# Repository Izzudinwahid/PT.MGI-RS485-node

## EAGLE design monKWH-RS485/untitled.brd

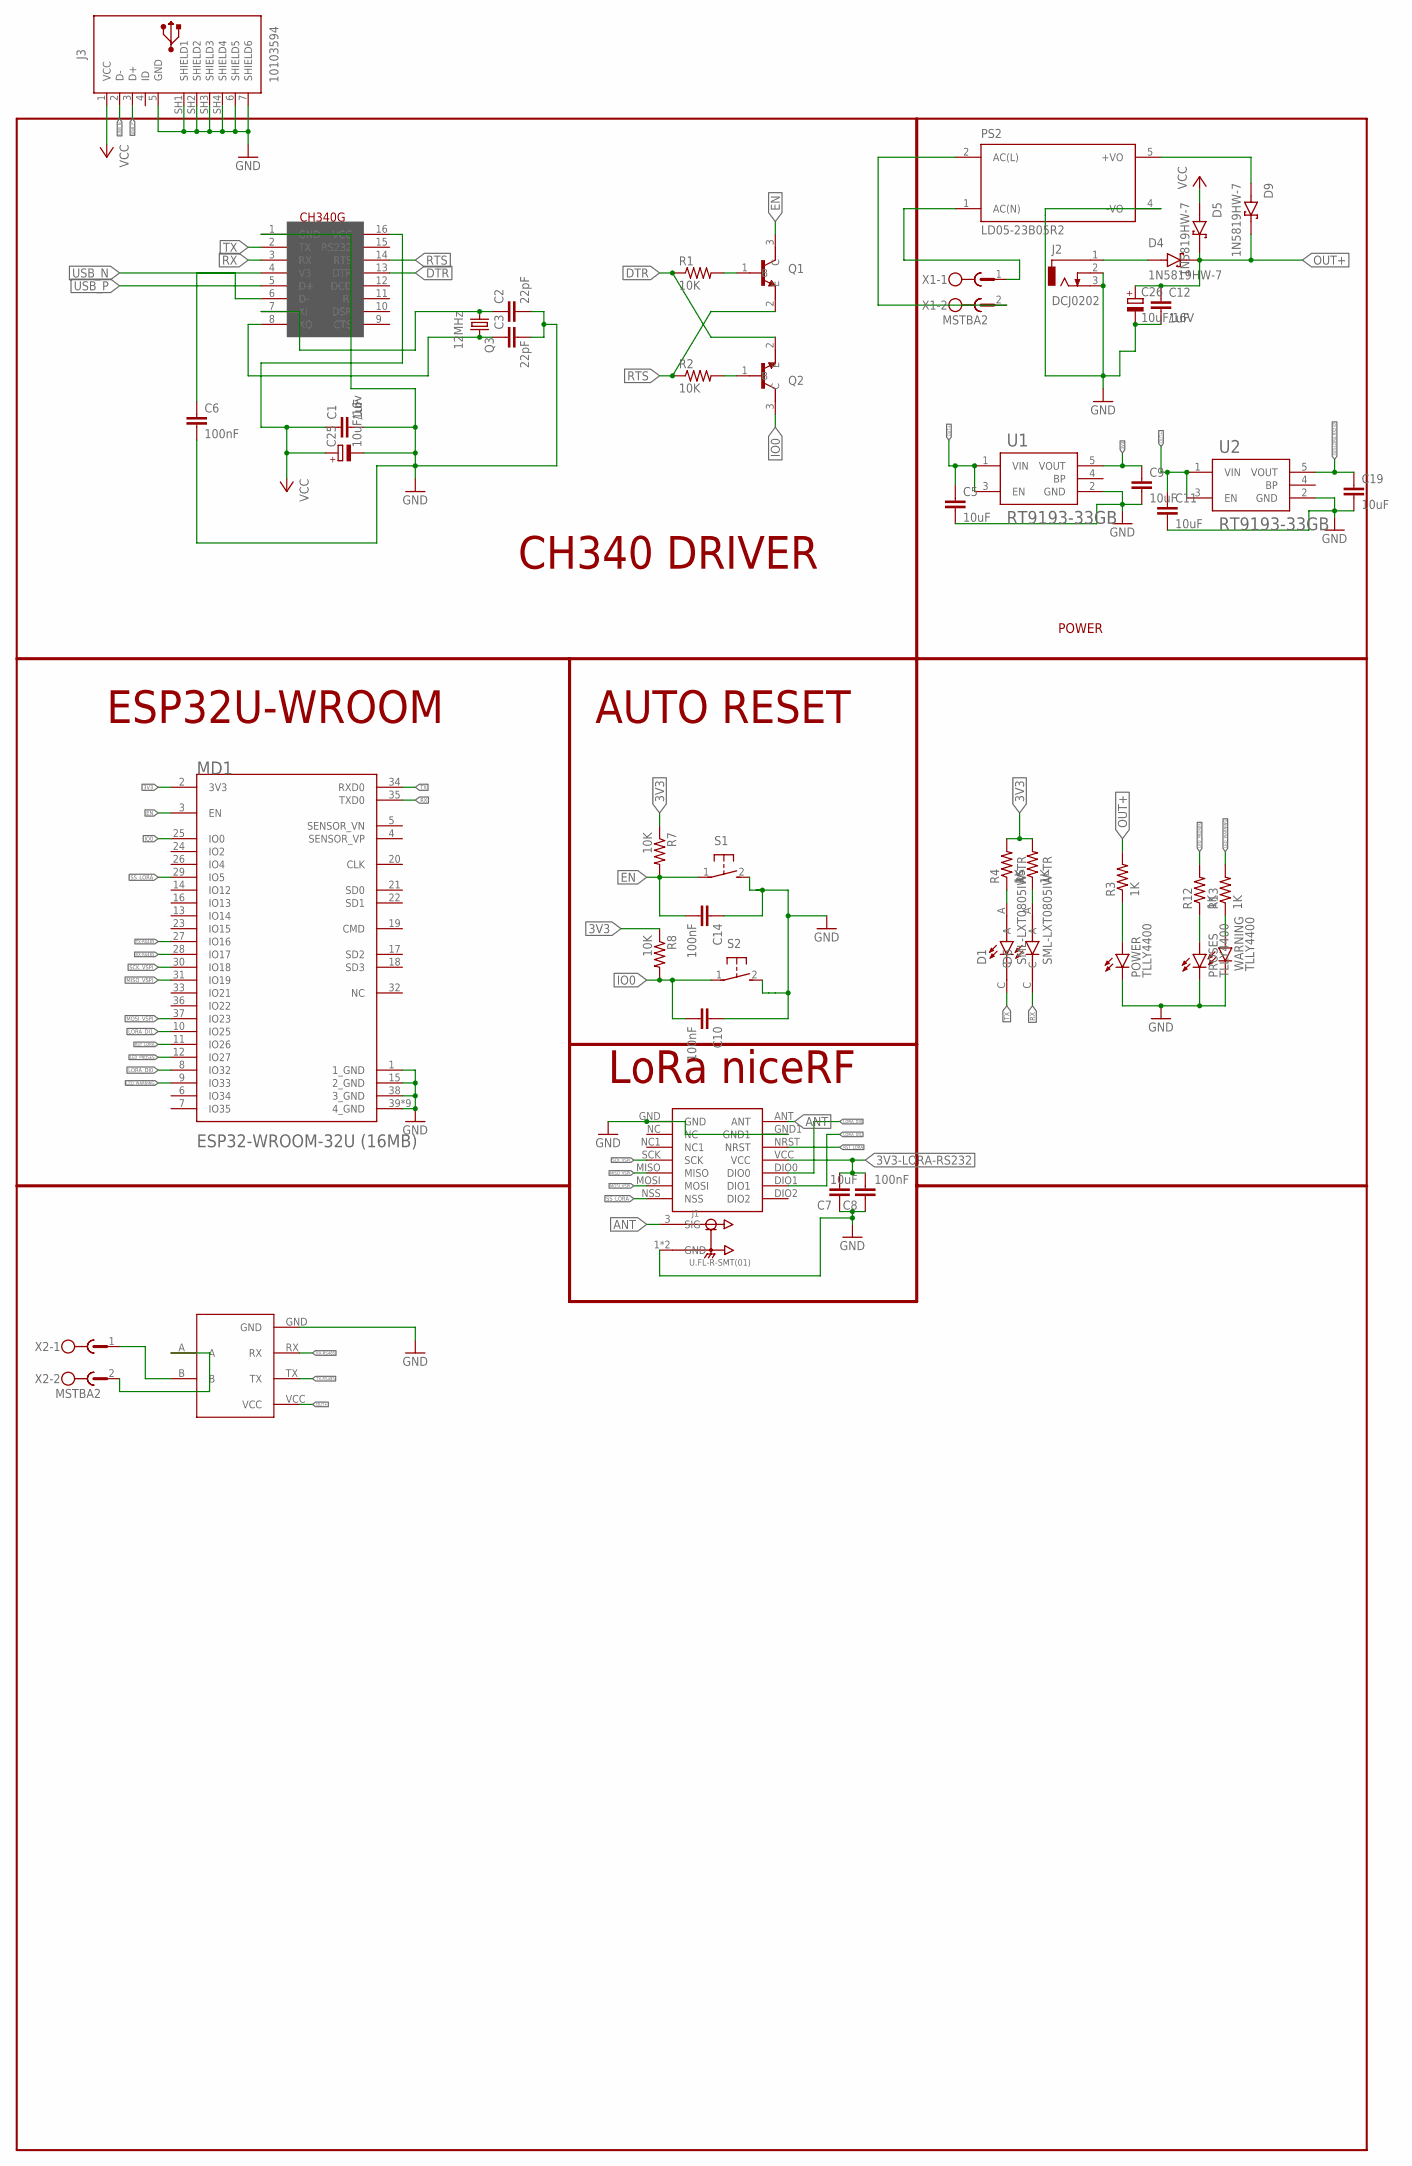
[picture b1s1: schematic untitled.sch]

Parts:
C1, C12: 1uF; C0805K
C2, C3: 22pF; C0805K
C5, C7, C9, C11, C19: 10uF; C0805K
C6, C8, C10, C14: 100nF; C0805K
C25: 10uF/16v; 153CLV-0505
C26: 10uF/16V; 153CLV-0505
D1, D6: SML-LXT0805IW-TR; LEDC2012X120N
D4, D5, D9: 1N5819HW-7; SOD3715X145N
J1: U.FL-R-SMT(01); HRS_U.FL-R-SMT(01)
J2: DCJ0202
J3: 10103594
LORA-NICERF-V1: LORA-NICERF-V2
MD1: ESPRESSIF_SYSTEMS_ESP32-WROOM-32U_16MBESPRESSIF_S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; ESPRESSIF_SYSTEMS_ESP32-WROOM-32U_16MB_0
POWER: TLLY4400; LED3MM
PROSES: TLLY4400; LED3MM
PS2: LD05-23B05R2; CONV_LD05-23B05R2
Q1, Q2: MMBT3904; SOT95P240X120-3N
Q3: 12MHz; SM49
R1, R2, R7, R8: 10K; M0805
R3, R4, R5, R12, R13: 1K; M0805
S1, S2: 31-XX; B3F-31XX
TTL-RS1: TTL-RS485
U1, U2: RT9193-33GB; SOT94P279X129-5N
U$2: CH340G; SOIC16
WARNING: TLLY4400; LED3MM
X1, X2: MSTBA2

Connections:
3V3: C9.1, MD1.2 (3V3), R4.2, R5.2, R7.1, R8.1, U1.5 (VOUT)
3V3-LORA-RS232: C7.2, C8.2, C19.1, LORA-NICERF-V1.VCC, U2.5 (VOUT)
ANT: J1.3 (SIG), LORA-NICERF-V1.ANT
DTR: Q2.2 (E), R1.1, U$2.13 (DTR)
EN: C14.2, MD1.3 (EN), Q1.3 (C), R7.2, S1.1
GND: C1.2, C2.2, C3.2, C5.2, C6.2, C7.1, C8.1, C9.2, C10.1, C11.2, C12.2, C14.1, C19.2, C25.-, C26.-, J1.1 (GND), J1.2 (GND), J2.2, J2.3, J3.5 (GND), J3.6 (SHIELD5), J3.7 (SHIELD6), J3.SH1 (SHIELD1), J3.SH2 (SHIELD2), J3.SH3 (SHIELD3), J3.SH4 (SHIELD4), LORA-NICERF-V1.GND, LORA-NICERF-V1.GND1, MD1.1 (1_GND), MD1.15 (2_GND), MD1.38 (3_GND), MD1.39 (4_GND), MD1.39-2 (4_GND), MD1.39-3 (4_GND), MD1.39-4 (4_GND), MD1.39-5 (4_GND), MD1.39-6 (4_GND), MD1.39-7 (4_GND), MD1.39-8 (4_GND), MD1.39-9 (4_GND), POWER.K (C), PROSES.K (C), PS2.4 (-VO), S1.2 (S), S2.2 (S), TTL-RS1.GND, U1.2 (GND), U2.2 (GND), U$2.1 (GND), WARNING.K (C)
IO0: C10.2, MD1.25 (IO0), Q2.3 (C), R8.2, S2.1
LED_PROSES: MD1.12 (IO27), R12.2
LED_WARNING: MD1.9 (IO33), R13.2
LORA_DI0: LORA-NICERF-V1.DIO0, MD1.8 (IO32)
LORA_DI1: LORA-NICERF-V1.DIO1, MD1.10 (IO25)
MISO_VSPI: LORA-NICERF-V1.MISO, MD1.31 (IO19)
MOSI_VSPI: LORA-NICERF-V1.MOSI, MD1.37 (IO23)
unnamed: C2.1, Q3.1, U$2.7 (XI)
unnamed: C3.1, Q3.2, U$2.8 (XO)
unnamed: POWER.A, R3.1
unnamed: Q1.1 (B), R1.2
unnamed: Q2.1 (B), R2.2
unnamed: D4.A, J2.1
unnamed: TTL-RS1.B, X2.1
unnamed: D1.A, R4.1
unnamed: D6.A, R5.1
unnamed: TTL-RS1.A, X2.2
unnamed: PS2.1 (AC(N)), X1.1
unnamed: C6.1, U$2.4 (V3)
unnamed: PS2.2 (AC(L)), X1.2
unnamed: D9.A, PS2.5 (+VO)
unnamed: PROSES.A, R12.1
unnamed: R13.1, WARNING.A
OUT+: C5.1, C11.1, C12.1, C26.+, D4.C (K), D5.C (K), D9.C (K), R3.2, TTL-RS1.VCC, U1.1 (VIN), U1.3 (EN), U2.1 (VIN), U2.3 (EN)
RST_LORA: LORA-NICERF-V1.NRST, MD1.11 (IO26)
RTS: Q1.2 (E), R2.1, U$2.14 (RTS)
RX: D6.C, MD1.35 (TXD0), U$2.3 (RX)
RX-RS485: MD1.28 (IO17), TTL-RS1.RX
SCK_VSPI: LORA-NICERF-V1.SCK, MD1.30 (IO18)
SS_LORA: LORA-NICERF-V1.NSS, MD1.29 (IO5)
TX: D1.C, MD1.34 (RXD0), U$2.2 (TX)
TX-RS485: MD1.27 (IO16), TTL-RS1.TX
USB_N: J3.2 (D-), U$2.6 (D-)
USB_P: J3.3 (D+), U$2.5 (D+)
VCC: C1.1, C25.+, D5.A, J3.1 (VCC), U$2.16 (VCC)

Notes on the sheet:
CH340 DRIVER
POWER
ESP32U-WROOM
AUTO RESET
LoRa niceRF

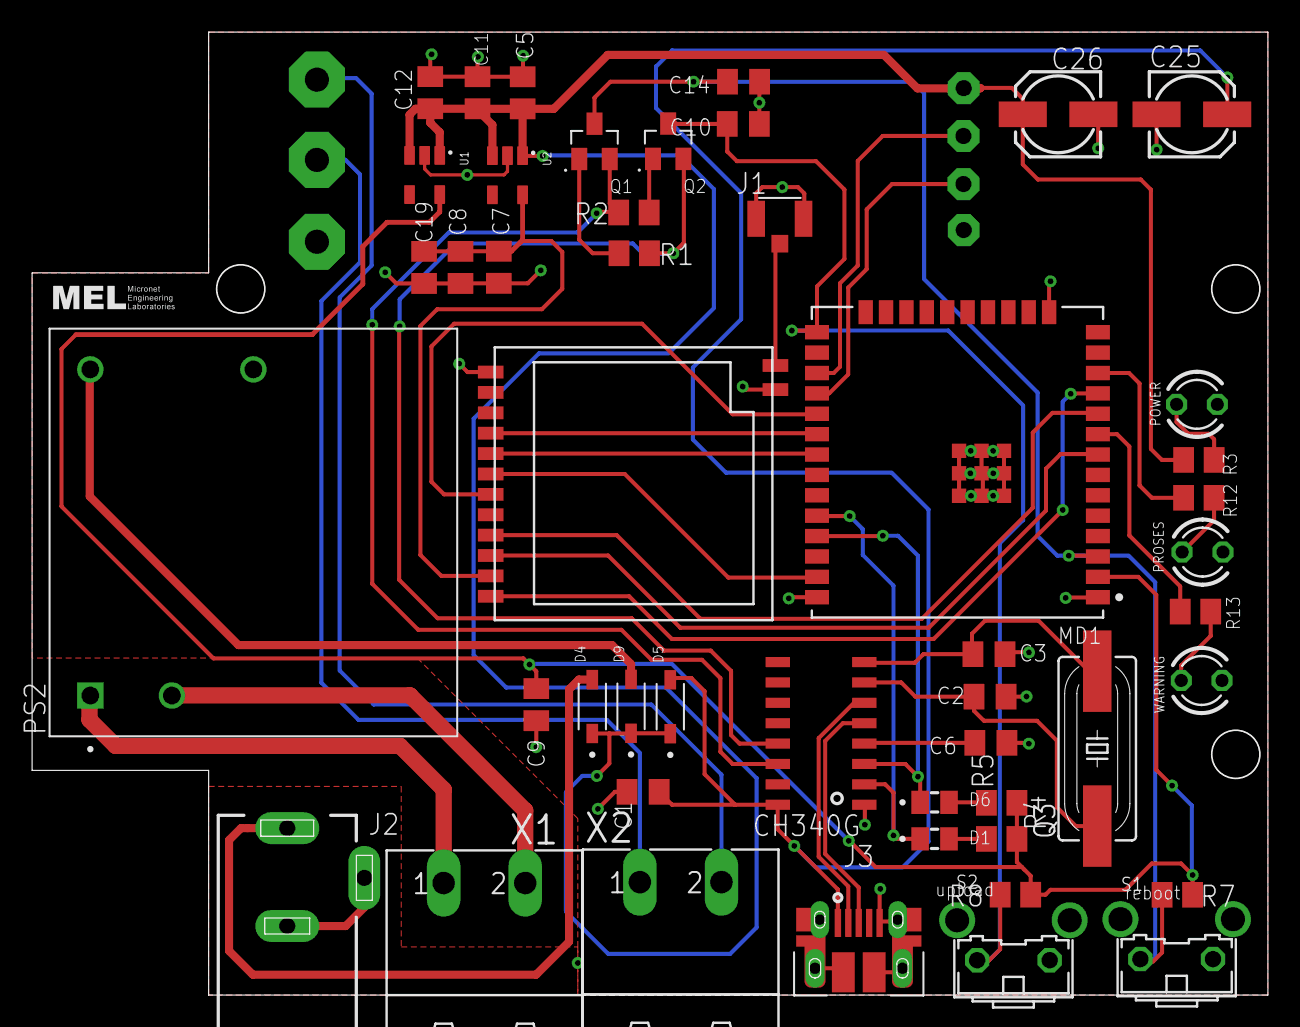
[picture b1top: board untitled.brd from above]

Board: 2 copper layers, 77.0 x 60.0 mm, 49 parts (1 on the bottom side), 41 nets.

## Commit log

2024-08-02 PCB V1.0
2024-08-02 PCBv1.0
